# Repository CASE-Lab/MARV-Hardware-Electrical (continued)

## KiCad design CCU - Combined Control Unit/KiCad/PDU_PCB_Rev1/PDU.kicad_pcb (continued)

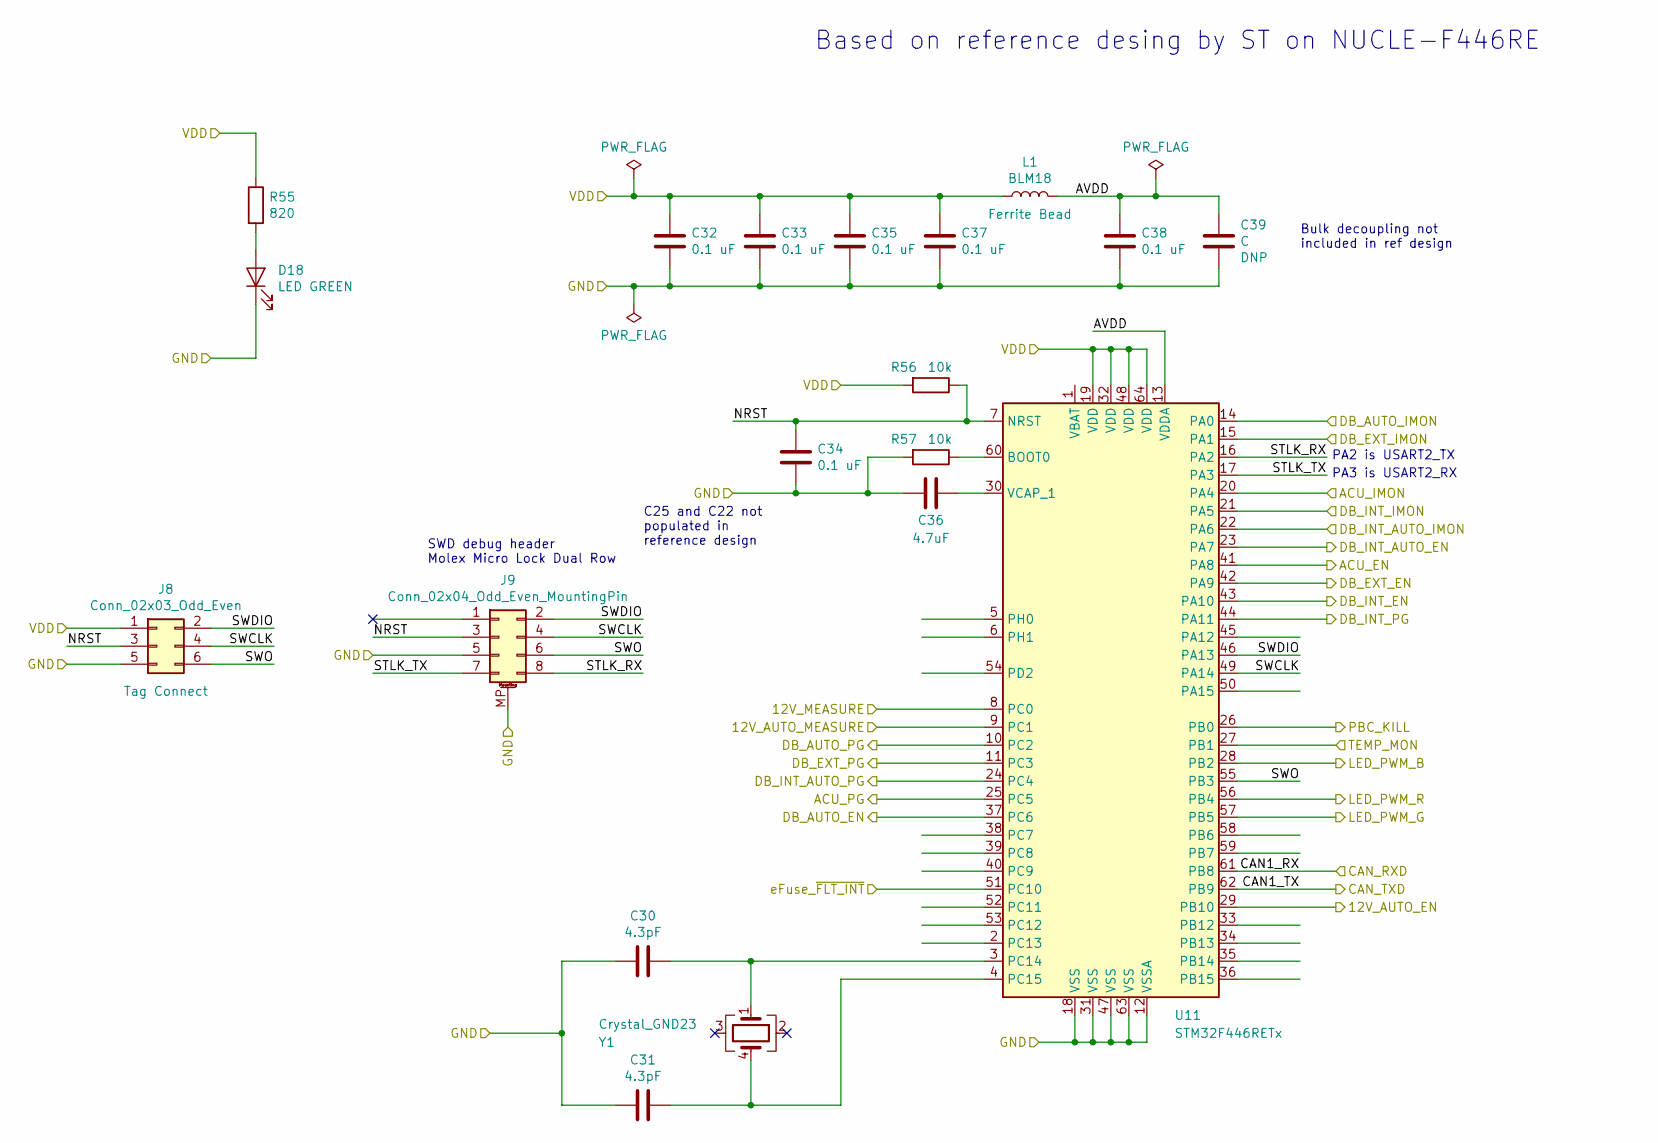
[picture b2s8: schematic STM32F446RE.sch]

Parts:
C30, C31: 4.3pF; C_0603_1608Metric
C32, C33, C34, C35, C37, C38: 0.1 uF; C_0603_1608Metric
C36: 4.7uF; C_0603_1608Metric
C39: C; C_0603_1608Metric
D18: LED GREEN; LED_0603_1608Metric
J8: Conn_02x03_Odd_Even; Tag-Connect_TC2030-IDC-NL_2x03_P1.27mm_Vertical
J9: Conn_02x04_Odd_Even_MountingPin; Molex_Micro-Lock_5054330871_2x4_P1.25_Vertical; MPN 538-505433-0871
L1: BLM18; L_0603_1608Metric; MPN BLM18PG471SN1D
R55: 820; R_0603_1608Metric
R56, R57: 10k; R_0603_1608Metric
U11: STM32F446RETx; LQFP-64_10x10mm_P0.5mm
Y1: Crystal_GND23; Crystal_SMD_Abracon_ABS25-4Pin_8.0x3.8mm; MPN ABS25-32.768KHZ-6-T

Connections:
+3V3: C32.1, C33.1, C35.1, C37.1, J8.1, L1.1, R55.1, R56.2, U11.19 (VDD), U11.32 (VDD), U11.48 (VDD), U11.64 (VDD); also elsewhere on the board
/12V_AUTO_EN: U11.29 (PB10); also elsewhere on the board
/12V_AUTO_MEASURE: U11.9 (PC1); also elsewhere on the board
/12V_MEASURE: U11.8 (PC0); also elsewhere on the board
/ACU_EN: U11.41 (PA8); also elsewhere on the board
/ACU_IMON: U11.20 (PA4); also elsewhere on the board
/ACU_PG: U11.25 (PC5); also elsewhere on the board
/DB_AUTO_EN: U11.37 (PC6); also elsewhere on the board
/DB_AUTO_IMON: U11.14 (PA0); also elsewhere on the board
/DB_AUTO_PG: U11.10 (PC2); also elsewhere on the board
/DB_EXT_EN: U11.42 (PA9); also elsewhere on the board
/DB_EXT_IMON: U11.15 (PA1); also elsewhere on the board
/DB_EXT_PG: U11.11 (PC3); also elsewhere on the board
/DB_INT_AUTO_EN: U11.23 (PA7); also elsewhere on the board
/DB_INT_AUTO_IMON: U11.22 (PA6); also elsewhere on the board
/DB_INT_AUTO_PG: U11.24 (PC4); also elsewhere on the board
/DB_INT_EN: U11.43 (PA10); also elsewhere on the board
/DB_INT_IMON: U11.21 (PA5); also elsewhere on the board
/DB_INT_PG: U11.44 (PA11); also elsewhere on the board
/PBC_KILL: U11.26 (PB0); also elsewhere on the board
/STM32F446RE/AVDD: C38.1, C39.1, L1.2, U11.13 (VDDA)
/STM32F446RE/CAN_RXD: U11.61 (PB8); also elsewhere on the board
/STM32F446RE/CAN_TXD: U11.62 (PB9); also elsewhere on the board
/STM32F446RE/NRST: C34.1, J8.3, J9.3, R56.1, U11.7 (NRST)
/STM32F446RE/STLK_RX: J9.8, U11.16 (PA2)
/STM32F446RE/STLK_TX: J9.7, U11.17 (PA3)
/STM32F446RE/SWCLK: J8.4, J9.4, U11.49 (PA14)
/STM32F446RE/SWDIO: J8.2, J9.2, U11.46 (PA13)
/STM32F446RE/SWO: J8.6, J9.6, U11.55 (PB3)
/S_LED_B_A: U11.28 (PB2); also elsewhere on the board
/S_LED_G_A: U11.57 (PB5); also elsewhere on the board
/S_LED_R_A: U11.56 (PB4); also elsewhere on the board
/TEMP_MON: U11.27 (PB1); also elsewhere on the board
/eFuse_~FLT: U11.51 (PC10); also elsewhere on the board
GND: C30.2, C31.2, C32.2, C33.2, C34.2, C35.2, C36.2, C37.2, C38.2, C39.2, D18.1 (K), J8.5, J9.5, J9.MP (MountPin), R57.2, U11.12 (VSSA), U11.18 (VSS), U11.31 (VSS), U11.47 (VSS), U11.63 (VSS); also elsewhere on the board
unnamed: C30.1, U11.3 (PC14), Y1.1
unnamed: C31.1, U11.4 (PC15), Y1.4
unnamed: C36.1, U11.30 (VCAP_1)
unnamed: D18.2 (A), R55.2
unnamed: R57.1, U11.60 (BOOT0)

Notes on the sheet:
C25 and C22 not populated in reference design
SWD debug header Molex Micro Lock Dual Row
Based on reference desing by ST on NUCLE-F446RE
PA3 is USART2_RX
PA2 is USART2_TX
Bulk decoupling not included in ref design

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
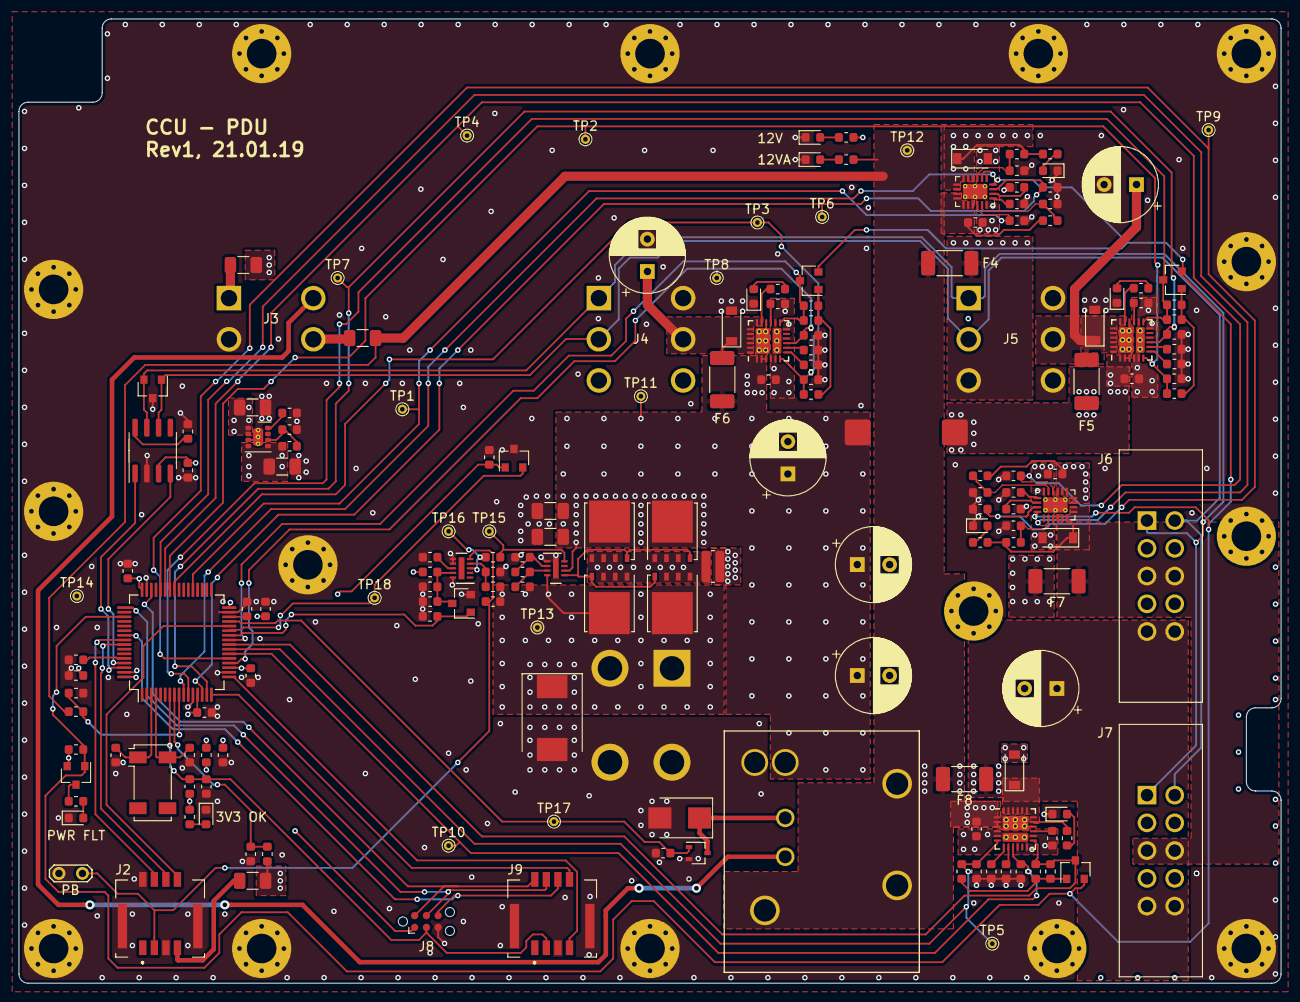
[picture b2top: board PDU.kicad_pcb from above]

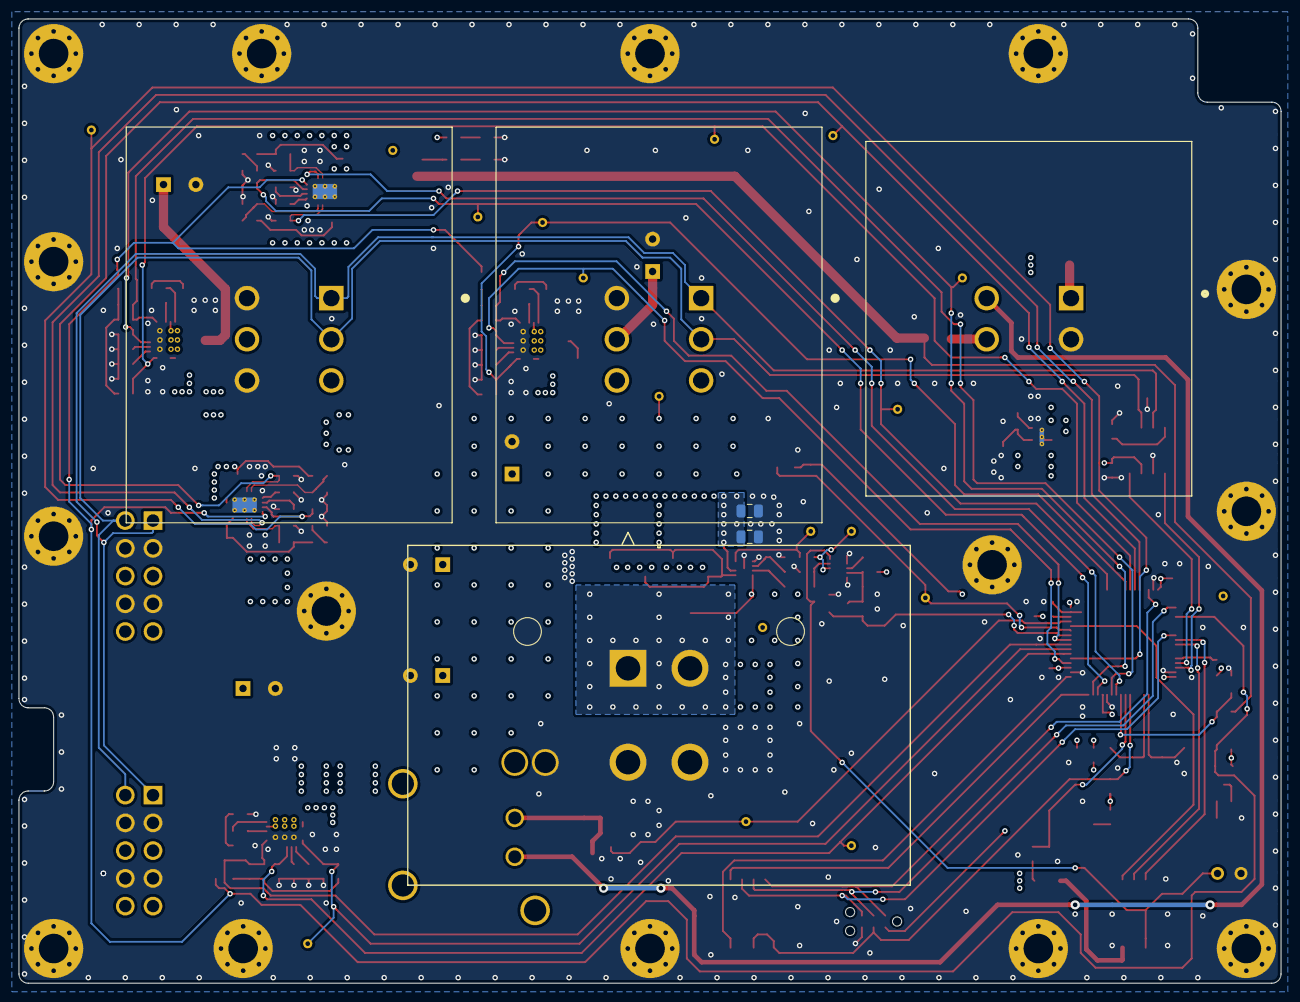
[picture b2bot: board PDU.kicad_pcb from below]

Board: 4 copper layers, 136.5 x 104.3 mm, 196 parts (6 on the bottom side), 97 nets.

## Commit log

2021-09-12 Create LICENSE
2021-11-03 added OCU top buttons to exsisting hardware adapter
2021-11-03 finished button adapter, started with power pcb
2021-11-05 finished board
2021-12-09 updated MCU power pcb
2022-08-03 Added LED driver PCBA
2022-08-22 added ibom files
